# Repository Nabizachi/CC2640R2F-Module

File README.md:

# CC2640R2F-Module
Dev board Ebyte E104-BT51 (CC2640R2F TI) <br/>
Печатная плата была спроектирована для написания первичного кода большого IoT проекта основанного на микроконтроллере CC2640R2F.<br/>
*[Сюда любые вопросы касательно этой печатной платы и/или, если вам нужно разработать плату для вашего проекта](https://www.upwork.com/freelancers/~01481c3fd0a27295ae?s=1110580753891577856)*<br/><br/><br/><br/>
Repository Contents<br/>
-------------------<br/>
- КД: Конструкторская документация (BOM, принципиальная схема, сборочный чертеж)<br/>
- Модель: 3D Модель в step формате, Gerber файлы для производства.<br/>
- Scheme: Исходники (KiCad)<br/>
- Информация: здесь я обычно храню даташиты и прочую инфу необходимую для проекта, в данном случае здесь ничего нет :)<br/><br/><br/><br/>
<div align="center">

<p>3D PCB Model</p>
</div><br>
<div align="center">

<p>PCB tracing</p>
</div>
<br/><br/><br/>
License Information<br/>
-------------------<br/>
THE BEER-WARE LICENSE<br/>
Nabizachi сделал эту плату. Вы можете делать с этим материалом все, что хотите. Если же мы когда-нибудь встретимся, и вы подумаете этот материал того стоит, вы можете купить мне бутылочку пива. Спасибо!

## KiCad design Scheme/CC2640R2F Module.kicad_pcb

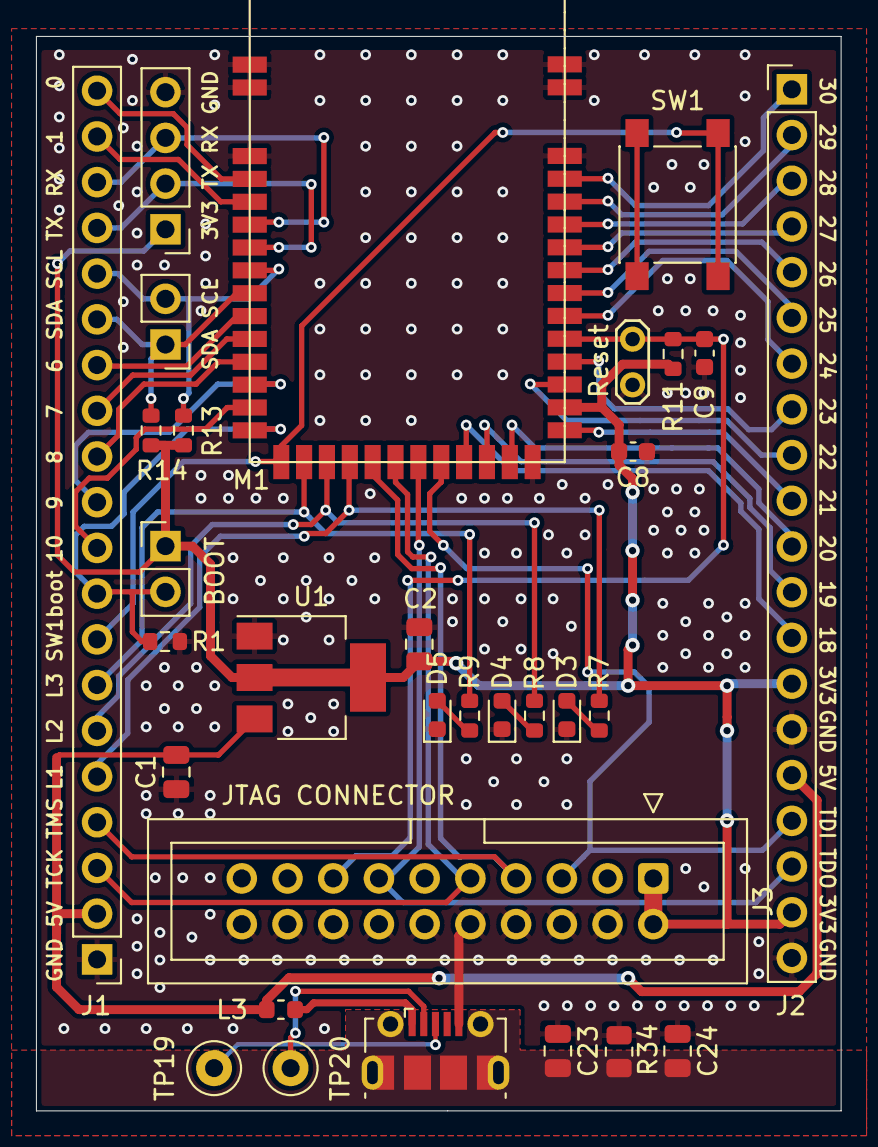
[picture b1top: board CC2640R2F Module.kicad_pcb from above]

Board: 2 copper layers, 44.7 x 59.7 mm, 31 parts (0 on the bottom side), 44 nets.

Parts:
3V3 TX RX GND: Conn_01x04_Male; PinHeader_1x04_P2.54mm_Vertical
BOOT: SW1; PinHeader_1x02_P2.54mm_Vertical
C1, C2: 10u; C_0805_2012Metric
C8, C9: 100n; C_0603_1608Metric
C23: 100n; C_0805_2012Metric
C24: 10n; C_0805_2012Metric
D3, D4, D5: LED_Small; LED_0603_1608Metric
J1, J2: Conn_01x20_Male; PinHeader_1x20_P2.54mm_Vertical
J3: Conn_ARM_JTAG_SWD_20; IDC-Header_2x10_P2.54mm_Vertical
JTAG CONNECTOR: USB_B_Micro; USB_Micro-B_Molex-105017-0001
L3: 600; L_0603_1608Metric
M1: E104-BT51
R1, R13, R14: 10K; R_0603_1608Metric
R7, R8, R9: 300R; R_0603_1608Metric
R11: 100K; R_0603_1608Metric
R34: 1M; R_0805_2012Metric
Reset: Reset; TestPoint_2Pads_Pitch2.54mm_Drill0.8mm
SDA SCL: Conn_01x02_Male; PinHeader_1x02_P2.54mm_Vertical
SW1: SW1; SW_Push_1P1T_NO_6x6mm_H9.5mm
TP19, TP20: TestPoint; TestPoint_Loop_D1.80mm_Drill1.0mm_Beaded
U1: LM1117-3.3; SOT-223

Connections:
+3V3: 3V3 TX RX GND.1, BOOT.1, C2.1, C8.2, J2.14, J2.19, J3.1, J3.2, M1.29, R11.2, R13.2, R14.2, U1.2, U1.4
+5V: C1.2, J1.2, J2.16, L3.2, U1.3
BOOT_ENABLE: BOOT.2, J1.9, M1.15, R1.1
D+: JTAG CONNECTOR.3, TP19.1
D-: JTAG CONNECTOR.2, TP20.1
DIO_0: J1.20, M1.4
DIO_1: J1.19, M1.5
DIO_6: J1.14, M1.10
DIO_7: J1.13, M1.11
DIO_8: J1.12, M1.12
DIO_9: J1.11, M1.13
DIO_10: J1.10, M1.14
DIO_18: J2.13, M1.24
DIO_19: J2.12, M1.25
DIO_20: J2.11, M1.26
DIO_21: J2.10, M1.28
DIO_22: J2.9, M1.30
DIO_23: J2.8, M1.31
DIO_24: J2.7, M1.33
DIO_25: J2.6, M1.34
DIO_26: J2.5, M1.35
DIO_27: J2.4, M1.36
DIO_28: J2.3, M1.37
DIO_29: J2.2, M1.38
DIO_30: J2.1, M1.39
GND: 3V3 TX RX GND.4, C1.1, C2.2, C8.1, C9.1, C23.1, C24.1, D3.1, D4.1, D5.1, J1.1, J2.15, J2.20, J3.4, J3.6, J3.8, J3.10, J3.12, J3.14, J3.16, J3.18, J3.20, JTAG CONNECTOR.5, M1.1, M1.2, M1.3, M1.27, M1.40, M1.41, M1.42, R1.2, R34.2, Reset.2, U1.1
I2C_SCL: J1.16, M1.8, R13.1, SDA SCL.2
I2C_SDA: J1.15, M1.9, R14.1, SDA SCL.1
JTAG_TCK: J1.3, J3.9, M1.21
JTAG_TDI: J2.17, J3.5, M1.23
JTAG_TDO: J2.18, J3.13, M1.22
JTAG_TMS: J1.4, J3.7, M1.20
LED_1: J1.5, M1.19, R7.2
LED_2: J1.6, M1.18, R8.2
LED_3: J1.7, M1.17, R9.2
unnamed: D3.2, R7.1
unnamed: D4.2, R8.1
unnamed: D5.2, R9.1
unnamed: JTAG CONNECTOR.1, L3.1
Shield: C23.2, C24.2, JTAG CONNECTOR.6, R34.1
UART_RX: 3V3 TX RX GND.3, J1.18, M1.6
UART_TX: 3V3 TX RX GND.2, J1.17, M1.7
WakeUP_Sleep: J1.8, M1.16, SW1.2
nReset: C9.2, J3.15, M1.32, R11.1, Reset.1

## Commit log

2022-01-19 second commit
